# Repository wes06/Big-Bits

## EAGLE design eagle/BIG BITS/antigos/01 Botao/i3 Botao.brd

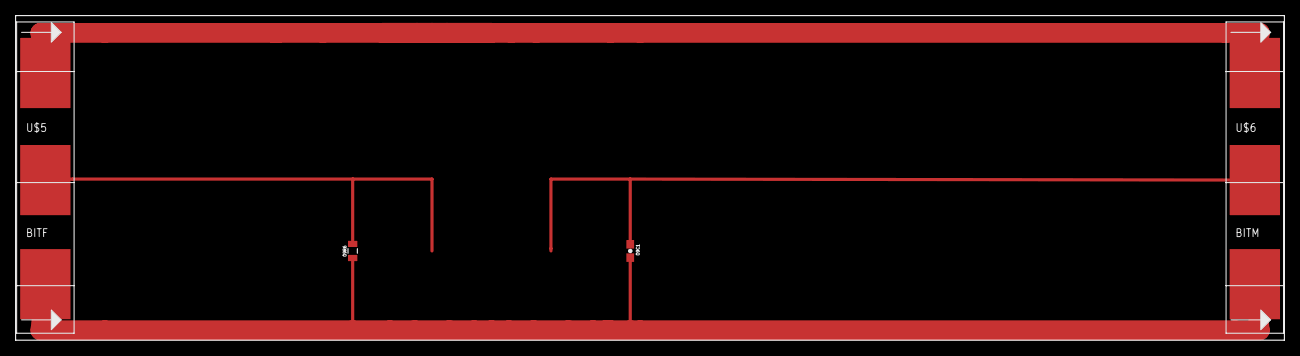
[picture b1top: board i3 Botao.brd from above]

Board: 2 copper layers, 162.5 x 41.6 mm, 6 parts (0 on the bottom side), 4 nets.

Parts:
O9C1: 0.1uF; 0603-CAP
O9R6: 1M; 0805
U$1: LB_CREDITS; OSHWCREDIT
U$3: OSHW-LOGOL; OSHW-LOGO-L
U$5: BITF; BITM
U$6: BITM

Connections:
GND: O9C1.2, O9R6.1, U$5.GND, U$6.GND
SIG: O9R6.2, U$5.SIG
SIGIN: O9C1.1, U$6.SIG
VCC: U$5.VCC, U$6.VCC

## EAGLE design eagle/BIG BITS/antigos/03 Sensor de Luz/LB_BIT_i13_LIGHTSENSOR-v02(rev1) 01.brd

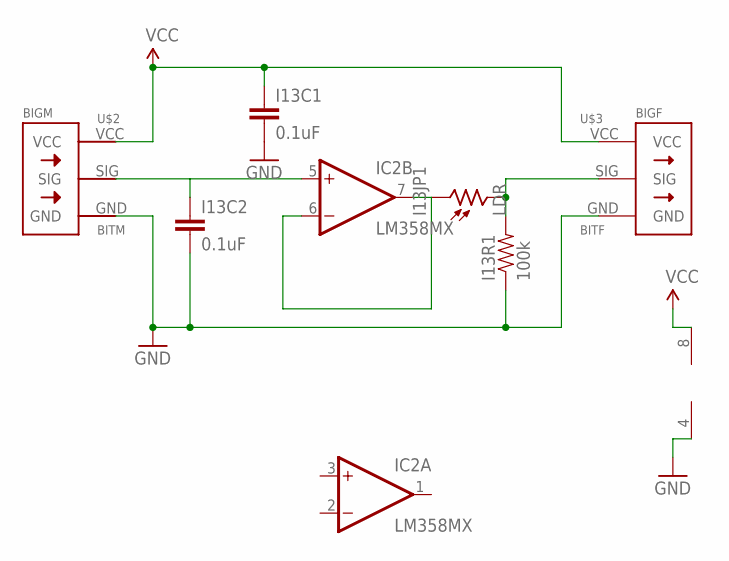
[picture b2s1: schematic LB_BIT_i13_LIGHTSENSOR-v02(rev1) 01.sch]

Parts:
I13C1, I13C2: 0.1uF; 1206
I13JP1: LDR; T0-46-A10XX
I13R1: 100k; 0805
IC2: LM358MX; SO08
U$2: BITM
U$3: BITF; BITM

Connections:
GND: I13C1.2, I13C2.2, I13R1.1, IC2.4 (V-), U$2.GND, U$3.GND
unnamed: I13JP1.1, IC2.6 (-IN), IC2.7 (OUT)
PS: I13JP1.2, I13R1.2, U$3.SIG
SIG: I13C2.1, IC2.5 (+IN), U$2.SIG
VCC: I13C1.1, IC2.8 (V+), U$2.VCC, U$3.VCC

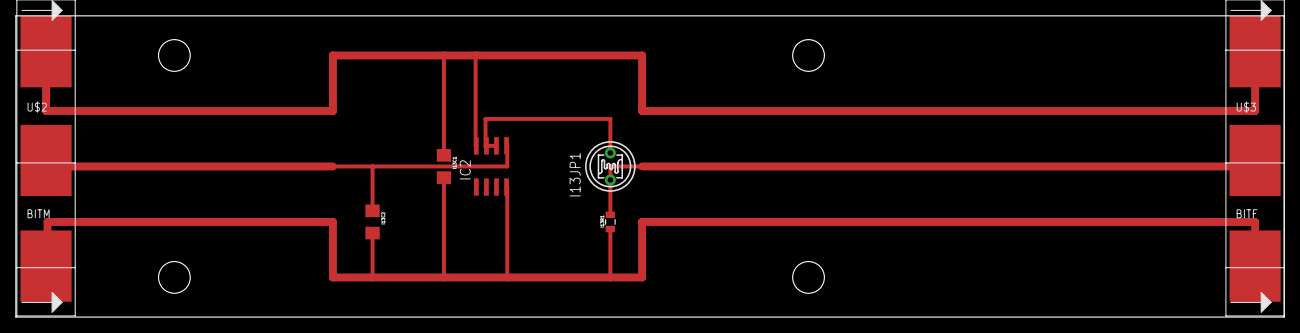
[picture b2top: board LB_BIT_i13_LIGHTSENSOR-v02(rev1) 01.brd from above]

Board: 2 copper layers, 160.0 x 38.0 mm, 7 parts (0 on the bottom side), 5 nets.

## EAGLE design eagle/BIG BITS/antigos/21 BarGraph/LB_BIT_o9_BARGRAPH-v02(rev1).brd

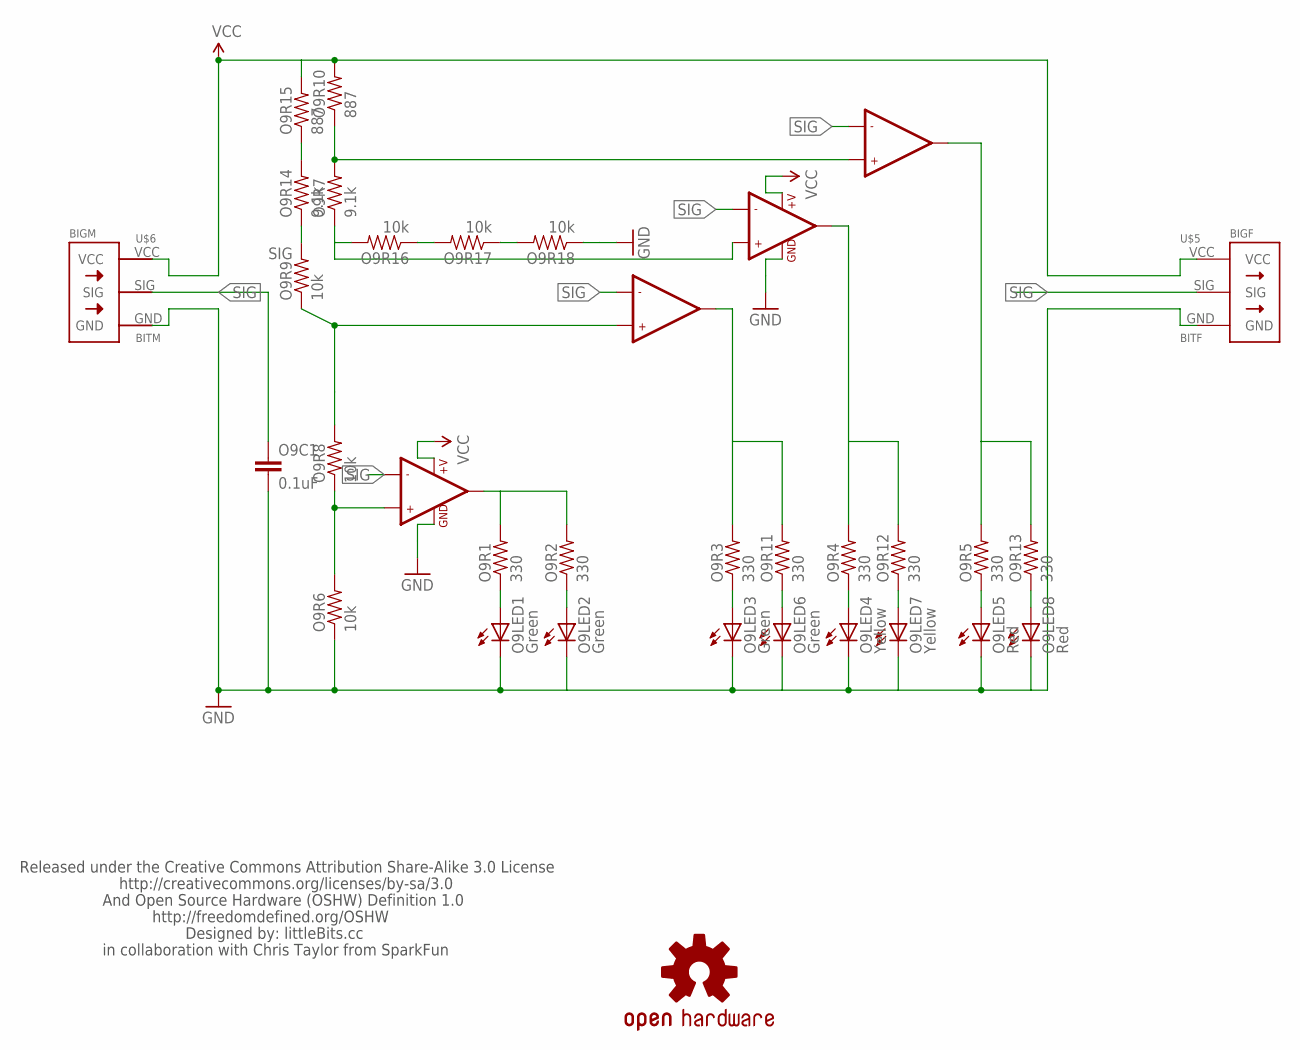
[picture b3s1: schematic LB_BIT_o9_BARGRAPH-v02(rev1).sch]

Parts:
O9C1: 0.1uF; 0603-CAP
O9LED1, O9LED2, O9LED3, O9LED6: Green; LED-1206
O9LED4, O9LED7: Yellow; LED-1206
O9LED5, O9LED8: Red; LED-1206
O9R1, O9R2, O9R3, O9R4, O9R5, O9R11, O9R12, O9R13: 330; 0805
O9R6, O9R8, O9R9, O9R16, O9R17, O9R18: 10k; 0805
O9R7, O9R14: 9.1k; 0805
O9R10, O9R15: 887; 0805
U$1: LB_CREDITS; OSHWCREDIT
U$2, U$4: LMV358; SO08
U$3: OSHW-LOGOL; OSHW-LOGO-L
U$5: BITF; BITM
U$6: BITM

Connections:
GND: O9C1.2, O9LED1.C, O9LED2.C, O9LED3.C, O9LED4.C, O9LED5.C, O9LED6.C, O9LED7.C, O9LED8.C, O9R6.1, O9R18.1, U$2.4 (GND), U$4.4 (GND), U$5.GND, U$6.GND
unnamed: O9R1.2, O9R2.2, U$2.1 (OUT1)
unnamed: O9LED1.A, O9R1.1
unnamed: O9R14.2, O9R15.1
unnamed: O9LED3.A, O9R3.1
unnamed: O9LED4.A, O9R4.1
unnamed: O9LED5.A, O9R5.1
unnamed: O9LED8.A, O9R13.1
unnamed: O9R9.2, O9R14.1
unnamed: O9LED7.A, O9R12.1
unnamed: O9LED6.A, O9R11.1
unnamed: O9R3.2, O9R11.2, U$2.7 (OUT2)
unnamed: O9R4.2, O9R12.2, U$4.1 (OUT1)
unnamed: O9R5.2, O9R13.2, U$4.7 (OUT2)
unnamed: O9R6.2, O9R8.1, U$2.3 (+IN1)
unnamed: O9R7.1, O9R16.2, U$4.3 (+IN1)
unnamed: O9R8.2, O9R9.1, U$2.5 (+IN2)
unnamed: O9R16.1, O9R17.2
unnamed: O9R17.1, O9R18.2
unnamed: O9LED2.A, O9R2.1
unnamed: O9R7.2, O9R10.1, U$4.5 (+IN2)
SIG: O9C1.1, U$2.2 (-IN1), U$2.6 (-IN2), U$4.2 (-IN1), U$4.6 (-IN2), U$5.SIG, U$6.SIG
VCC: O9R10.2, O9R15.2, U$2.8 (+V), U$4.8 (+V), U$5.VCC, U$6.VCC

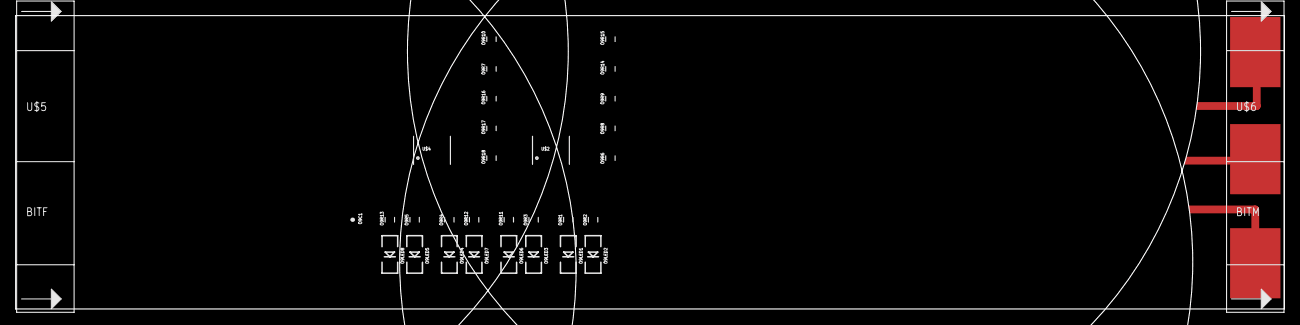
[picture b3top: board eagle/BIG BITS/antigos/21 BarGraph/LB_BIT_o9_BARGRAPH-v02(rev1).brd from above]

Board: 2 copper layers, 162.5 x 37.6 mm, 33 parts (0 on the bottom side), 23 nets.

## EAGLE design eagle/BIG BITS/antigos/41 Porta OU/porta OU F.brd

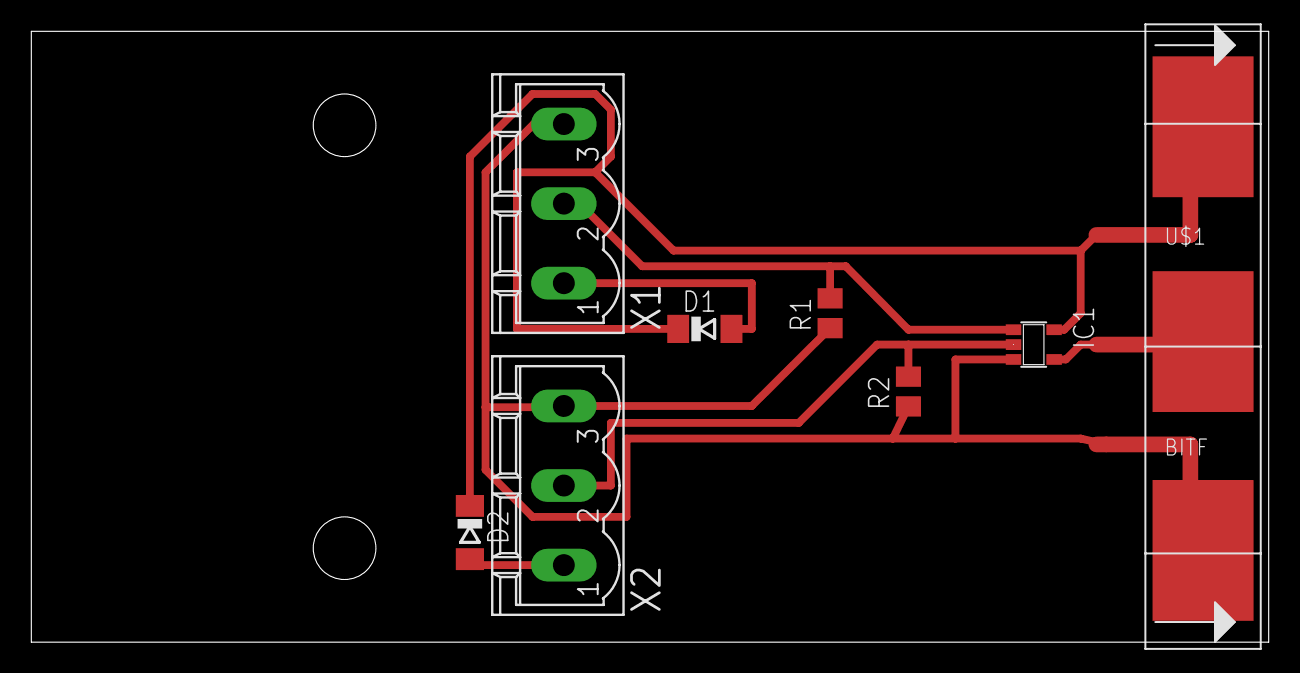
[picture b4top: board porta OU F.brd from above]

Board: 2 copper layers, 79.0 x 39.0 mm, 8 parts (0 on the bottom side), 7 nets.

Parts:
D1, D2: SOD80C
IC1: 74AHC1G32DBV; SOT23-5
R1, R2: 1M; M0805
U$1: BITF; BITM
X1, X2: MSTBV3

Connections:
GND: IC1.3, R1.1, R2.1, U$1.GND, X1.3, X2.3
unnamed: D1.A, X1.1
unnamed: D2.A, X2.1
unnamed: IC1.4, U$1.SIG
SIG1: IC1.1, R1.2, X1.2
SIG2: IC1.2, R2.2, X2.2
VCC: D1.C, D2.C, IC1.5, U$1.VCC

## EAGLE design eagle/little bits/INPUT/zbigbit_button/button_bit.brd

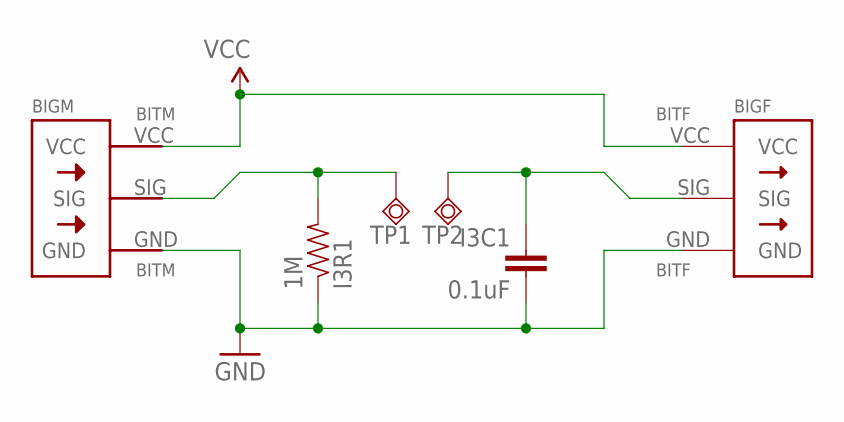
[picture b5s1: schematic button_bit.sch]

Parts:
BITF: BITF; BITM
BITM: BITM
I3C1: 0.1uF; 1206
I3R1: 1M; 0603-RES
TP1, TP2: TPSQTP20SQ; TP20SQ

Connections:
GND: BITF.GND, BITM.GND, I3C1.2, I3R1.1
SIG: BITM.SIG, I3R1.2, TP1.TP
SIG2: BITF.SIG, I3C1.1, TP2.TP
VCC: BITF.VCC, BITM.VCC

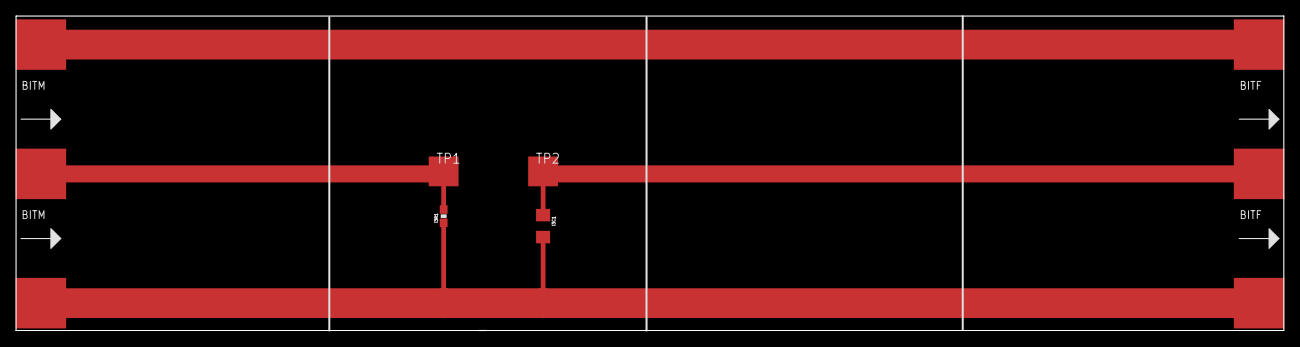
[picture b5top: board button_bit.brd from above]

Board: 2 copper layers, 161.9 x 40.2 mm, 6 parts (0 on the bottom side), 4 nets.

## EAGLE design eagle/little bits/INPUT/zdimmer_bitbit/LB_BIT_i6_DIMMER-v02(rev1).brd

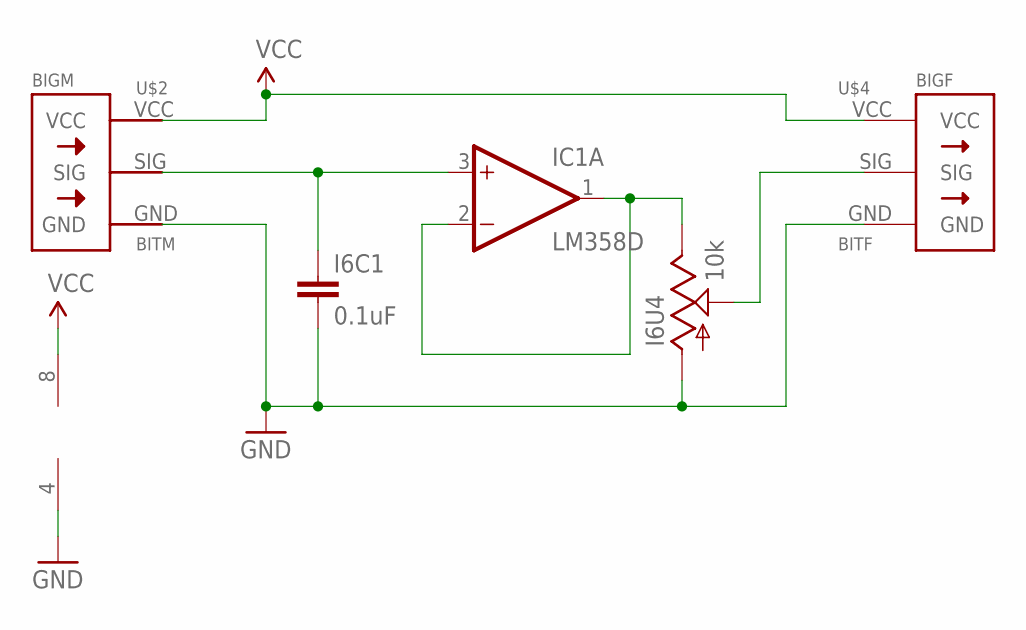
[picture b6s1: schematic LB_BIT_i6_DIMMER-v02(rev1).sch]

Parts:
I6C1: 0.1uF; 1206
I6U4: 10k; POT_ALPHA_RV16AF-20
IC1: LM358D; SO08
U$2: BITM
U$4: BITF; BITM

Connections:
GND: I6C1.2, I6U4.1 (A), IC1.4 (V-), U$2.GND, U$4.GND
unnamed: I6U4.3 (E), IC1.1 (OUT), IC1.2 (-IN)
POT: I6U4.2 (S), U$4.SIG
SIG: I6C1.1, IC1.3 (+IN), U$2.SIG
VCC: IC1.8 (V+), U$2.VCC, U$4.VCC

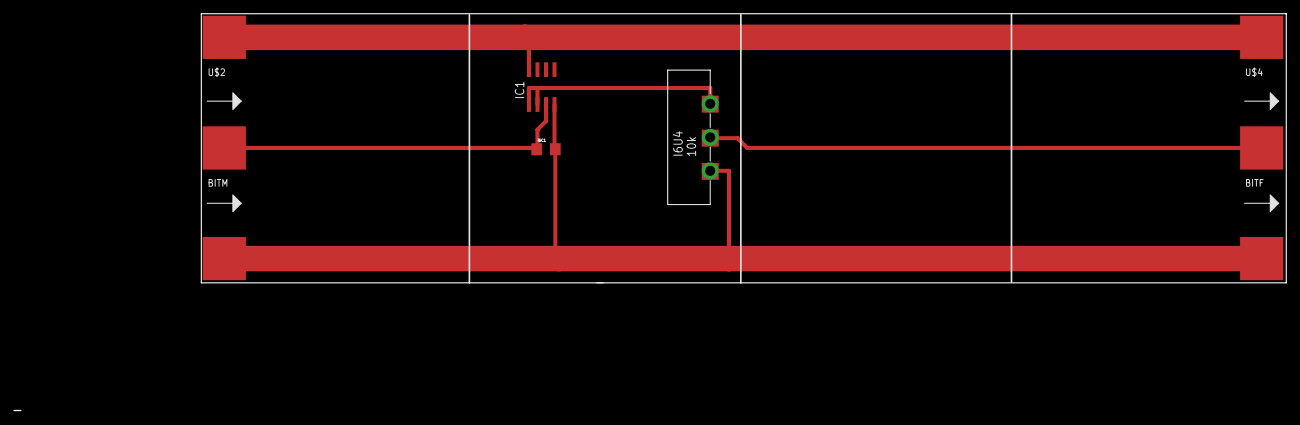
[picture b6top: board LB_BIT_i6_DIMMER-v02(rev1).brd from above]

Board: 2 copper layers, 161.9 x 40.2 mm, 5 parts (0 on the bottom side), 5 nets.

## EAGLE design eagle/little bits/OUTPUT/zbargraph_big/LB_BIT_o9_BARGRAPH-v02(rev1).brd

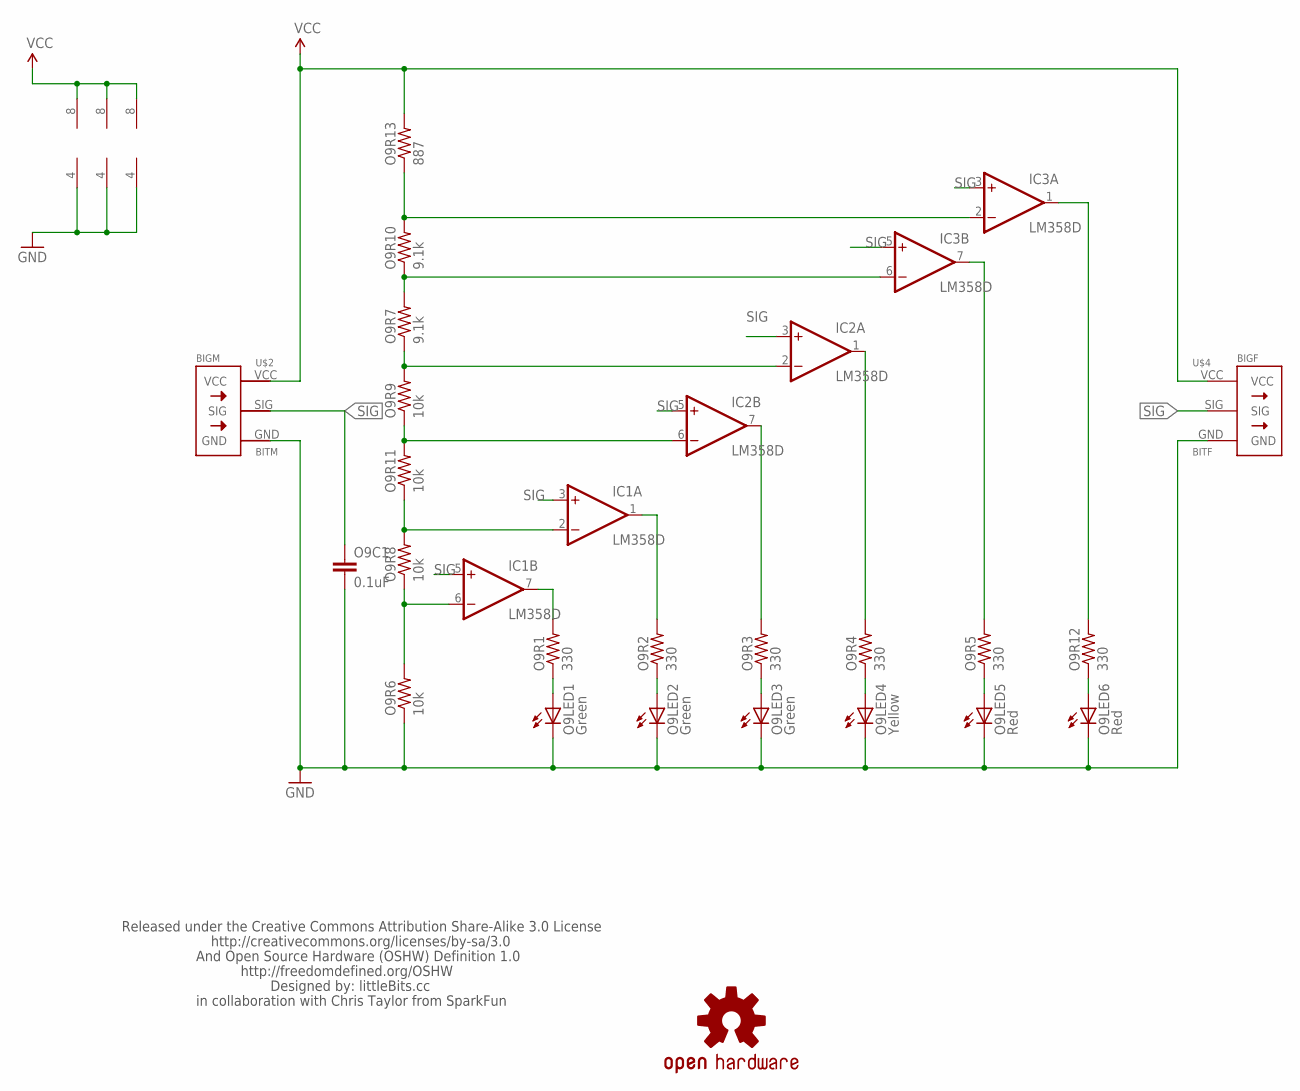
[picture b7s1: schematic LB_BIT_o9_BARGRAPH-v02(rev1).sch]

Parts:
IC1, IC2, IC3: LM358D; SO08
O9C1: 0.1uF; 1206
O9LED1, O9LED2, O9LED3: Green; LED-1206
O9LED4: Yellow; LED-1206
O9LED5, O9LED6: Red; LED-1206
O9R1, O9R2, O9R3, O9R4, O9R5, O9R12: 330; 0805
O9R6, O9R8, O9R9, O9R11: 10k; 0805
O9R7, O9R10: 9.1k; 0805
O9R13: 887; 0805
U$1: LB_CREDITS; OSHWCREDIT
U$2: BITM
U$3: OSHW-LOGOL; OSHW-LOGO-L
U$4: BITF; BITM

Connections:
GND: IC1.4 (V-), IC2.4 (V-), IC3.4 (V-), O9C1.2, O9LED1.C, O9LED2.C, O9LED3.C, O9LED4.C, O9LED5.C, O9LED6.C, O9R6.1, U$2.GND, U$4.GND
unnamed: IC1.7 (OUT), O9R1.2
unnamed: O9LED1.A, O9R1.1
unnamed: O9LED2.A, O9R2.1
unnamed: O9LED3.A, O9R3.1
unnamed: O9LED4.A, O9R4.1
unnamed: O9LED5.A, O9R5.1
unnamed: O9LED6.A, O9R12.1
unnamed: IC1.1 (OUT), O9R2.2
unnamed: IC2.7 (OUT), O9R3.2
unnamed: IC2.1 (OUT), O9R4.2
unnamed: IC3.1 (OUT), O9R12.2
unnamed: IC3.7 (OUT), O9R5.2
unnamed: IC1.6 (-IN), O9R6.2, O9R8.1
unnamed: IC1.2 (-IN), O9R8.2, O9R11.1
unnamed: IC2.6 (-IN), O9R9.1, O9R11.2
unnamed: IC2.2 (-IN), O9R7.1, O9R9.2
unnamed: IC3.2 (-IN), O9R10.2, O9R13.1
unnamed: IC3.6 (-IN), O9R7.2, O9R10.1
SIG: IC1.3 (+IN), IC1.5 (+IN), IC2.3 (+IN), IC2.5 (+IN), IC3.3 (+IN), IC3.5 (+IN), O9C1.1, U$2.SIG, U$4.SIG
VCC: IC1.8 (V+), IC2.8 (V+), IC3.8 (V+), O9R13.2, U$2.VCC, U$4.VCC

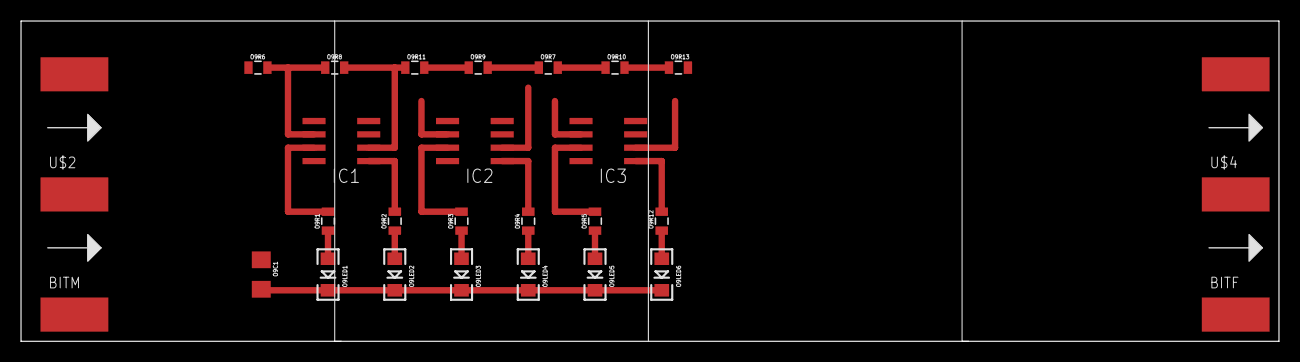
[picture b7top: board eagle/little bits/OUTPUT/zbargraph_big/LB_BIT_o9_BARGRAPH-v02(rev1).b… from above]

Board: 2 copper layers, 119.7 x 30.5 mm, 27 parts (0 on the bottom side), 21 nets.

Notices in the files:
parts and their libraries:
LITTLEBITS: Released under the Creative Commons Attribution Share-Alike 3.0 License
LITTLEBITS: http://creativecommons.org/license/by-sa/3.0
LITTLEBITS: http://creativecommons.org/licenses/by-sa/3.0
